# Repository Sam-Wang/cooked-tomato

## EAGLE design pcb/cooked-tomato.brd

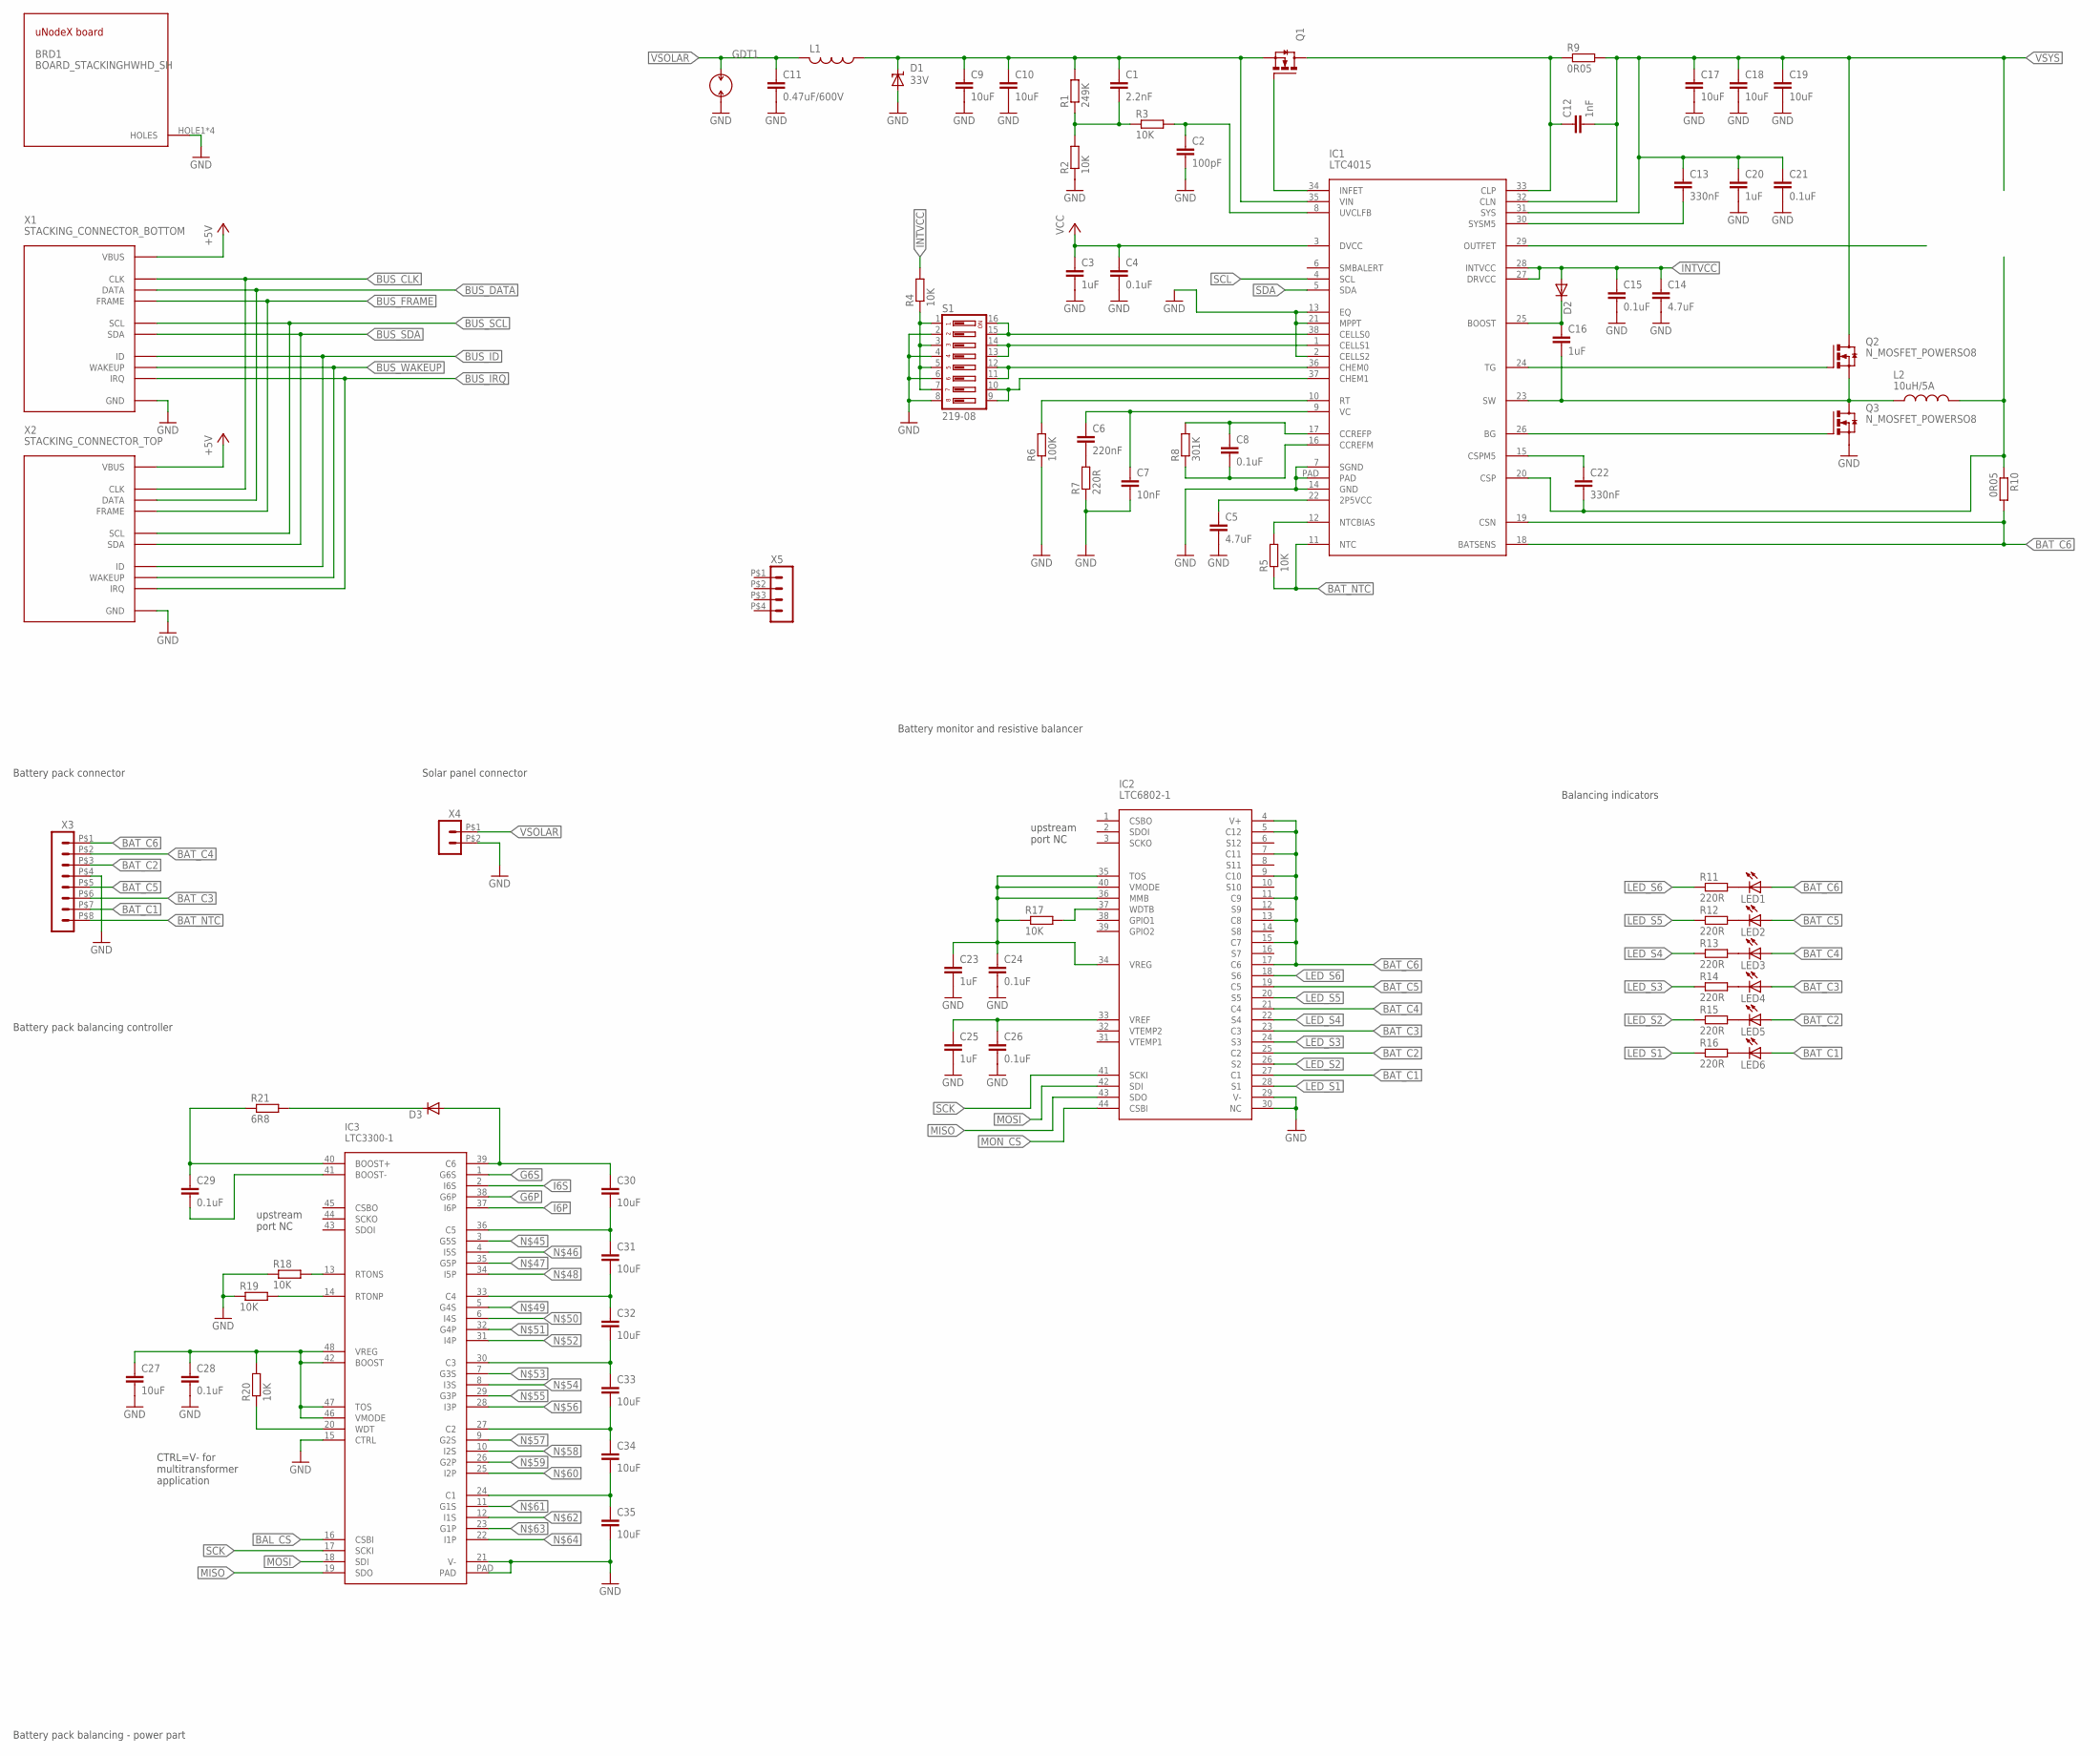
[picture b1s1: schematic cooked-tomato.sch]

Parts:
BRD1: BOARD_STACKINGHWHD_SH; HWHD_SHARP_CORNERS
C1: 2.2nF; C0603
C2: 100pF; C0603
C3, C16: 1uF; C0603
C4, C8, C15, C21, C24, C26, C28, C29: 0.1uF; C0603
C5, C14: 4.7uF; C0805
C6: 220nF; C0603
C7: 10nF; C0603
C9, C10, C17, C18, C19: 10uF; C2220K
C11: 0.47uF/600V; C1206
C12: 1nF; C0603
C13, C22: 330nF; C0603
C20, C23, C25: 1uF; C0805
C27: 10uF; C0805
C30, C31, C32, C33, C34, C35: 10uF; C1206
D1: 33V; SMBJ
D2, D3: DIODE-SOD323-W; SOD323-W
GDT1: 2035-09-SM-RPLF
IC1: LTC4015; QFN38
IC2: LTC6802-1; SSOP44
IC3: LTC3300-1; LQFP48
L1: L-USL4532P; L4532P
L2: 10uH/5A; L7070
LED1, LED2, LED3, LED4, LED5, LED6: LEDCHIP-LED0805; CHIP-LED0805
Q1, Q2, Q3: N_MOSFET_POWERSO8; POWERSO8
R1: 249K; R0603
R2, R3, R4, R5, R17, R18, R19, R20: 10K; R0603
R6: 100K; R0603
R7, R11, R12, R13, R14, R15, R16: 220R; R0603
R8: 301K; R0603
R9, R10: 0R05; R2512
R21: 6R8; R0603
S1: 219-08; CTS-219-08
X1: STACKING_CONNECTOR_BOTTOM; HAR-FLEX-BOTTOM-12P
X2: STACKING_CONNECTOR_TOP; HAR-FLEX-TOP-12P
X3: HEADER_POS8_43045-0800; 43045-0800
X4: HEADER_POS2_43650-0200; 43650-0200
X5: HEADER_POS4_43045-0401; 43045-0400

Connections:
+5V: X1.VBUS, X2.VBUS
BAL_CS: IC3.16 (CSBI)
BAT_C1: IC2.27 (C1), LED6.A, X3.P$7 (7)
BAT_C2: IC2.25 (C2), LED5.A, X3.P$3 (3)
BAT_C3: IC2.23 (C3), LED4.A, X3.P$6 (6)
BAT_C4: IC2.21 (C4), LED3.A, X3.P$2 (2)
BAT_C5: IC2.19 (C5), LED2.A, X3.P$5 (5)
BAT_C6: IC1.18 (BATSENS), IC1.19 (CSN), IC2.4 (V+), IC2.5 (C12), IC2.7 (C11), IC2.9 (C10), IC2.11 (C9), IC2.13 (C8), IC2.15 (C7), IC2.17 (C6), LED1.A, R10.2, X3.P$1 (1)
BAT_NTC: IC1.11 (NTC), R5.1, X3.P$8 (8)
BUS_CLK: X1.CLK, X2.CLK
BUS_DATA: X1.DATA, X2.DATA
BUS_FRAME: X1.FRAME, X2.FRAME
BUS_ID: X1.ID, X2.ID
BUS_IRQ: X1.IRQ, X2.IRQ
BUS_SCL: X1.SCL, X2.SCL
BUS_SDA: X1.SDA, X2.SDA
BUS_WAKEUP: X1.WAKEUP, X2.WAKEUP
CELLS0: IC1.38 (CELLS0), S1.15, S1.16
CELLS1: IC1.1 (CELLS1), S1.13, S1.14
CHEM0: IC1.36 (CHEM0), S1.11, S1.12
CHEM1: IC1.37 (CHEM1), S1.9, S1.10
G6P: IC3.38 (G6P)
G6S: IC3.1 (G6S)
GND: BRD1.HOLE1, BRD1.HOLE2, BRD1.HOLE3, BRD1.HOLE4, C2.2, C3.2, C4.2, C5.2, C7.2, C9.2, C10.2, C11.2, C14.2, C15.2, C17.2, C18.2, C19.2, C20.2, C21.2, C23.2, C24.2, C25.2, C26.2, C27.2, C28.2, C35.2, D1.A, GDT1.2, IC1.2 (CELLS2), IC1.7 (SGND), IC1.13 (EQ), IC1.14 (GND), IC1.21 (MPPT), IC1.PAD, IC2.29 (V-), IC2.30 (NC), IC3.15 (CTRL), IC3.21 (V-), IC3.PAD, Q3.1 (S), Q3.2 (S), Q3.3 (S), R2.1, R6.1, R7.1, R18.1, R19.1, S1.2, S1.4, S1.6, S1.8, X1.GND1 (GND), X1.GND2 (GND), X1.GND3 (GND), X1.H1 (GND), X1.H2 (GND), X1.H3 (GND), X1.H4 (GND), X2.GND1 (GND), X2.GND2 (GND), X2.GND3 (GND), X2.H1 (GND), X2.H2 (GND), X2.H3 (GND), X2.H4 (GND), X3.P$4 (4), X4.P$2 (2)
I6P: IC3.37 (I6P)
I6S: IC3.2 (I6S)
INTVCC: C14.1, C15.1, D2.A, IC1.27 (DRVCC), IC1.28 (INTVCC), R4.2
LED_S1: IC2.28 (S1), R16.1
LED_S2: IC2.26 (S2), R15.1
LED_S3: IC2.24 (S3), R14.1
LED_S4: IC2.22 (S4), R13.1
LED_S5: IC2.20 (S5), R12.1
LED_S6: IC2.18 (S6), R11.1
MISO: IC2.43 (SDO), IC3.19 (SDO)
MON_CS: IC2.44 (CSBI)
MOSI: IC2.42 (SDI), IC3.18 (SDI)
unnamed: IC1.34 (INFET), Q1.4 (G)
unnamed: C13.2, IC1.30 (SYSM5)
unnamed: C2.1, IC1.8 (UVCLFB), R3.2
unnamed: C1.2, R1.1, R2.2, R3.1
unnamed: IC1.12 (NTCBIAS), R5.2
unnamed: C5.1, IC1.22 (2P5VCC)
unnamed: IC1.10 (RT), R6.2
unnamed: C6.2, R7.2
unnamed: LED2.C, R12.2
unnamed: R4.1, S1.1, S1.3, S1.5, S1.7
unnamed: C6.1, C7.1, IC1.9 (VC)
unnamed: C8.1, IC1.17 (CCREFP), R8.2
unnamed: C8.2, IC1.16 (CCREFM), R8.1
unnamed: C1.1, C9.1, C10.1, D1.C, IC1.35 (VIN), L1.1, Q1.1 (S), Q1.2 (S), Q1.3 (S), R1.2
unnamed: C12.1, IC1.33 (CLP), Q1.5 (D), Q1.6 (D), Q1.7 (D), Q1.8 (D), Q1.PAD (D), R9.1
unnamed: IC1.24 (TG), Q2.4 (G)
unnamed: C16.1, D2.C, IC1.25 (BOOST)
unnamed: C16.2, IC1.23 (SW), L2.1, Q2.1 (S), Q2.2 (S), Q2.3 (S), Q3.5 (D), Q3.6 (D), Q3.7 (D), Q3.8 (D), Q3.PAD (D)
unnamed: IC1.26 (BG), Q3.4 (G)
unnamed: LED3.C, R13.2
unnamed: LED4.C, R14.2
unnamed: C22.2, IC1.20 (CSP), L2.2, R10.1
unnamed: C22.1, IC1.15 (CSPM5)
unnamed: LED5.C, R15.2
unnamed: LED6.C, R16.2
unnamed: C25.1, C26.1, IC2.33 (VREF)
unnamed: IC3.13 (RTONS), R18.2
unnamed: LED1.C, R11.2
unnamed: C23.1, C24.1, IC2.34 (VREG), IC2.35 (TOS), IC2.36 (MMB), IC2.40 (VMODE), R17.1
unnamed: IC2.37 (WDTB), R17.2
unnamed: IC3.14 (RTONP), R19.2
unnamed: IC3.20 (WDT), R20.1
unnamed: C27.1, C28.1, IC3.42 (BOOST), IC3.46 (VMODE), IC3.47 (TOS), IC3.48 (VREG), R20.2
unnamed: C29.2, IC3.41 (BOOST-)
unnamed: C29.1, IC3.40 (BOOST+), R21.1
unnamed: D3.C, R21.2
unnamed: C30.1, D3.A, IC3.39 (C6)
unnamed: C30.2, C31.1, IC3.36 (C5)
unnamed: C31.2, C32.1, IC3.33 (C4)
unnamed: C32.2, C33.1, IC3.30 (C3)
unnamed: C33.2, C34.1, IC3.27 (C2)
unnamed: C34.2, C35.1, IC3.24 (C1)
SCK: IC2.41 (SCKI), IC3.17 (SCKI)
SCL: IC1.4 (SCL)
SDA: IC1.5 (SDA)
VCC: C3.1, C4.1, IC1.3 (DVCC)
VSOLAR: C11.1, GDT1.1, L1.2, X4.P$1 (1)
VSYS: C12.2, C13.1, C17.1, C18.1, C19.1, C20.1, C21.1, IC1.31 (SYS), IC1.32 (CLN), Q2.5 (D), Q2.6 (D), Q2.7 (D), Q2.8 (D), Q2.PAD (D), R9.2

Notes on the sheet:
upstream port NC
Battery monitor and resistive balancer
Balancing indicators
Battery pack connector
Solar panel connector
CTRL=V- for multitransformer application
Battery pack balancing controller
Battery pack balancing - power part

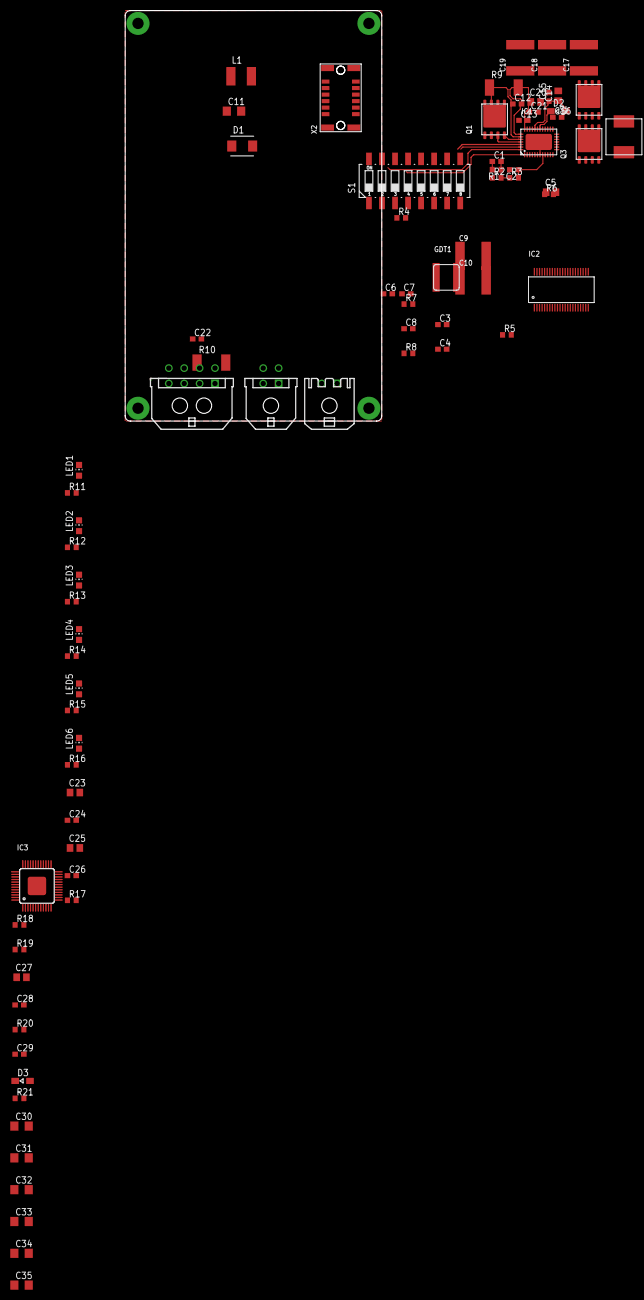
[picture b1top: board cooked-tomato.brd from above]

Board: 2 copper layers, 50.0 x 80.0 mm, 81 parts (0 on the bottom side), 76 nets.

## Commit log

2017-10-02 Add .gitignore file to ignore temporary Eagle files
2017-10-02 Add LTC4015 charger with components
2017-10-02 Add LTC3300 balancer and LTC6802 monitor schematic
